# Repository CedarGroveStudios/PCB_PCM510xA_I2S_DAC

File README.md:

# PCM510xA I2S Stereo DAC

### 

An I2S stereo audio DAC with an internal master clock PLL and a charge pump for direct-coupled ground-centered audio output.

[Adafruit Playground Article](https://adafruit-playground.com/u/CGrover/pages/pcm510xa-i2s-stereo-dac-breakout)

[Schematic](https://github.com/CedarGroveStudios/PCB_PCM510xA_I2S_DAC/blob/main/PCB/PCM510xA_I2S_DAC.pdf)

OSH Park PCB:
[https://oshpark.com/shared_projects/a6rQdBe2](https://oshpark.com/shared_projects/WVrOgntC)

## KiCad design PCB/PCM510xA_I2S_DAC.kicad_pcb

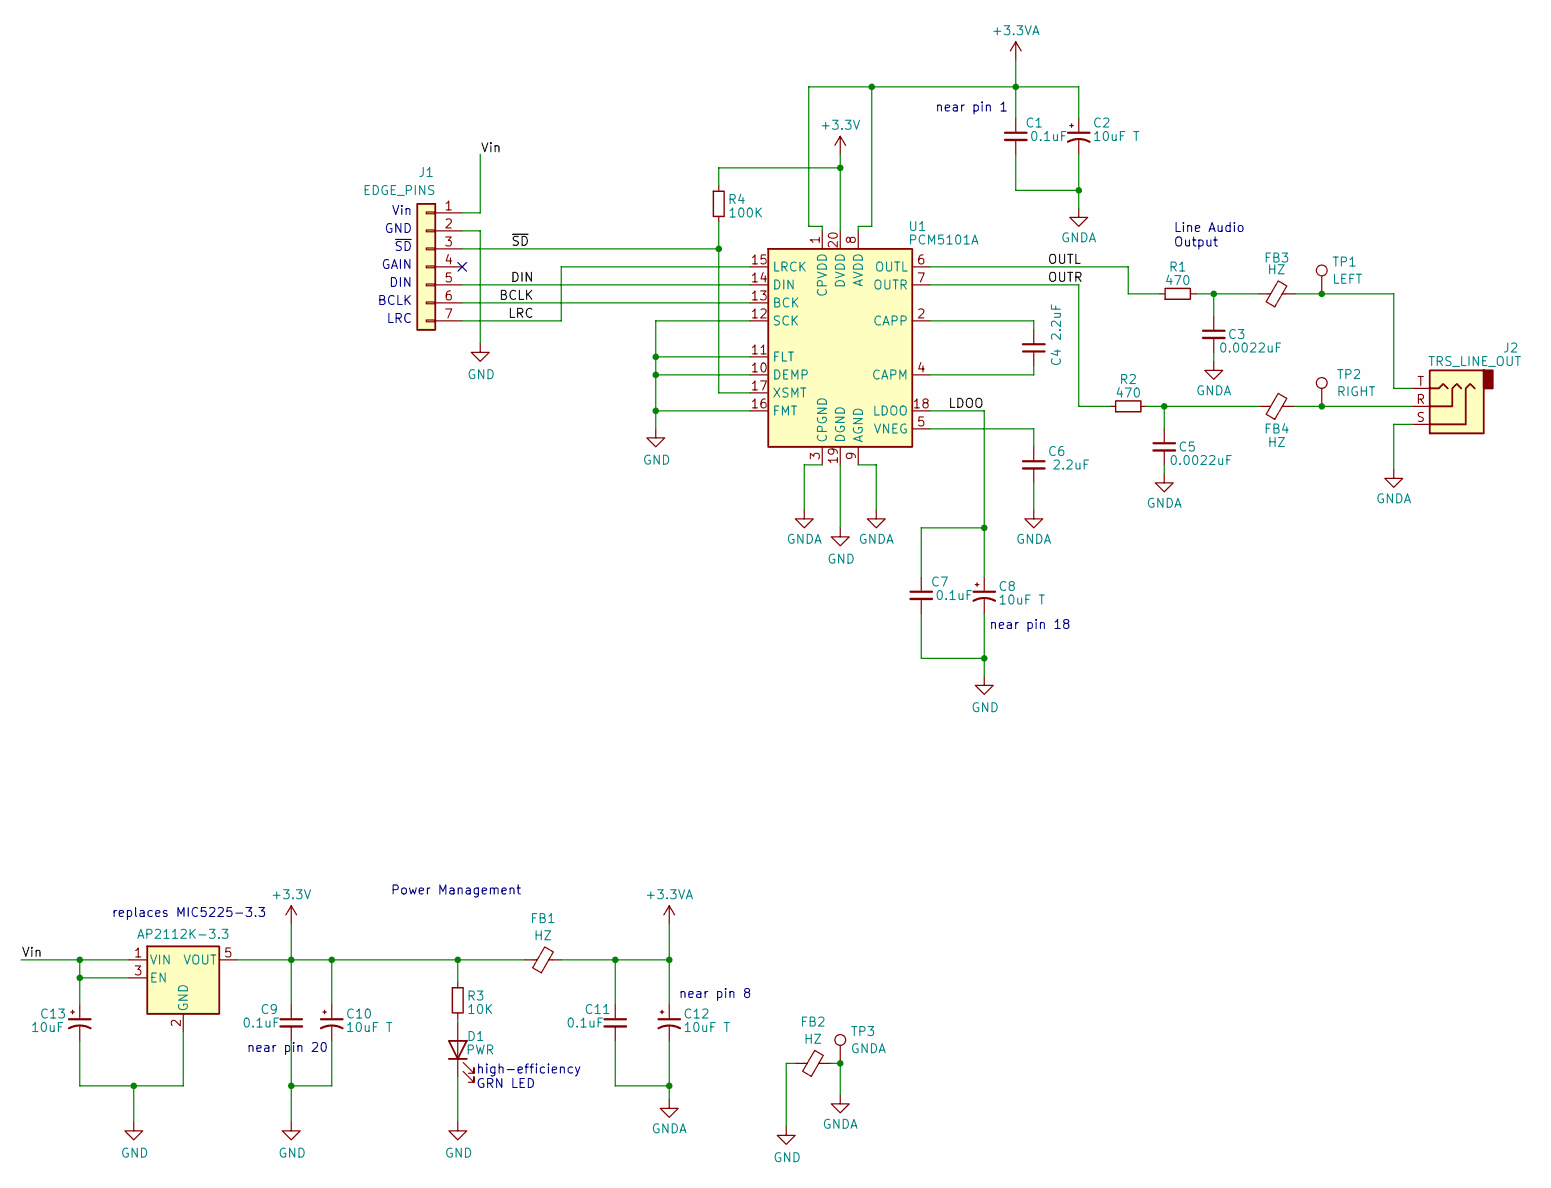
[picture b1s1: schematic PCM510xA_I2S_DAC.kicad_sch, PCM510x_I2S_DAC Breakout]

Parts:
C1, C7, C9, C11: 0.1uF; C_0805_2012Metric
C2, C8, C10, C12: 10uF T; C_0805_2012Metric
C3, C5: 0.0022uF; C_0805_2012Metric
C4, C6: 2.2uF; C_0805_2012Metric
C13: 10uF; C_0805_2012Metric
D1: PWR; LED_0805_2012Metric
FB1, FB2, FB3, FB4: HZ; R_0805_2012Metric
J1: EDGE_PINS; PinSocket_1x07_P2.54mm_Vertical
J2: TRS_LINE_OUT; Jack_3.5mm_CUI_SJ-3523-SMT_Horizontal
R1, R2: 470; R_0805_2012Metric
R3: 10K; R_0805_2012Metric
R4: 100K; R_0805_2012Metric
TP1: LEFT; TestPoint_Pad_2.0x2.0mm
TP2: RIGHT; TestPoint_Pad_2.0x2.0mm
TP3: GNDA; TestPoint_Pad_2.0x2.0mm
U1: PCM5101A; TSSOP-20_4.4x6.5mm_P0.65mm
U2: AP2112K-3.3; SOT-23-5

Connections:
+3.3V: C9.1, C10.1, FB1.1, R3.1, R4.1, U1.20 (DVDD), U2.5 (VOUT)
+3.3VA: C1.1, C2.1, C11.1, C12.1, FB1.2, U1.1 (CPVDD), U1.8 (AVDD)
/BCLK: J1.6, U1.13 (BCK)
/DIN: J1.5, U1.14 (DIN)
/LDOO: C7.1, C8.1, U1.18 (LDOO)
/LRC: J1.7, U1.15 (LRCK)
/OUTL: R1.1, U1.6 (OUTL)
/OUTR: R2.1, U1.7 (OUTR)
/Vin: C13.1, J1.1, U2.1 (VIN), U2.3 (EN)
/~SD: J1.3, R4.2, U1.17 (XSMT)
GND: C7.2, C8.2, C9.2, C10.2, C13.2, D1.1 (K), FB2.1, J1.2, U1.10 (DEMP), U1.11 (FLT), U1.12 (SCK), U1.16 (FMT), U1.19 (DGND), U2.2 (GND)
GNDA: C1.2, C2.2, C3.2, C5.2, C6.2, C11.2, C12.2, FB2.2, J2.S, TP3.1, U1.3 (CPGND), U1.9 (AGND)
unnamed: C3.1, FB3.1, R1.2
unnamed: C5.1, FB4.1, R2.2
unnamed: D1.2 (A), R3.2
unnamed: FB3.2, J2.T, TP1.1
unnamed: FB4.2, J2.R, TP2.1
unnamed: C4.1, U1.4 (CAPM)
unnamed: C4.2, U1.2 (CAPP)
unnamed: C6.1, U1.5 (VNEG)

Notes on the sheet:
replaces MIC5225-3.3
GND
high-efficiency GRN LED
LRC
near pin 1
Vin
DIN
Line Audio Output
near pin 18
near pin 20
Power Management
BCLK
GAIN
~{SD}
near pin 8

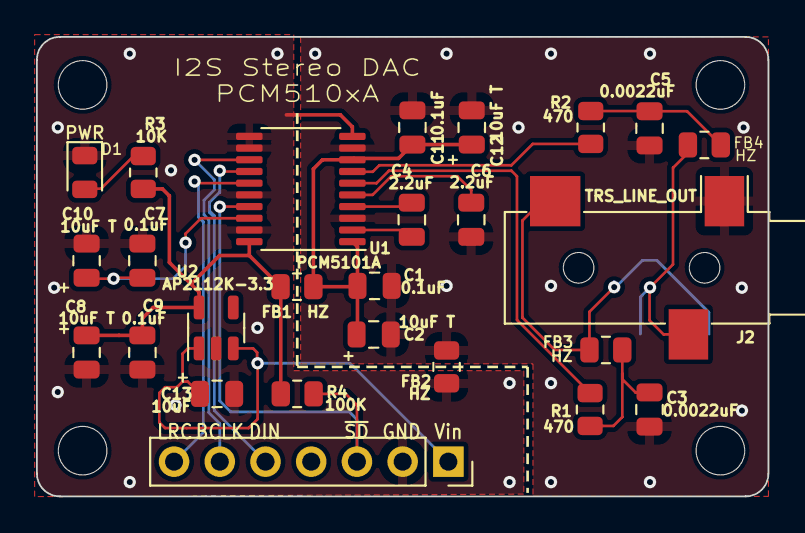
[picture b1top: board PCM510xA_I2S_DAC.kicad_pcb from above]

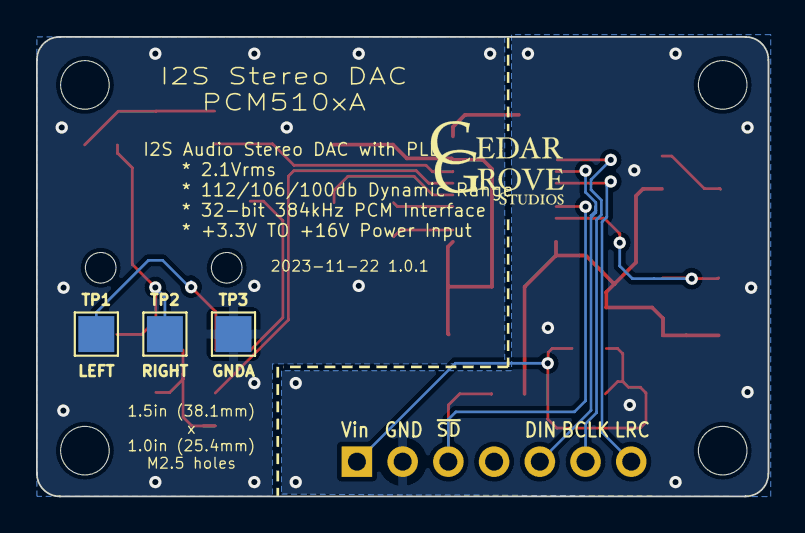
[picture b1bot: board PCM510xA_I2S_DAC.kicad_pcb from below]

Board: 2 copper layers, 40.6 x 25.5 mm, 29 parts (3 on the bottom side), 20 nets.

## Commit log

2023-10-18 initial repo load
2023-11-22 update 3.3v regulator
2023-11-22 update gerbers and bom
2023-11-23 update docs
2024-01-05 update design; update backups
